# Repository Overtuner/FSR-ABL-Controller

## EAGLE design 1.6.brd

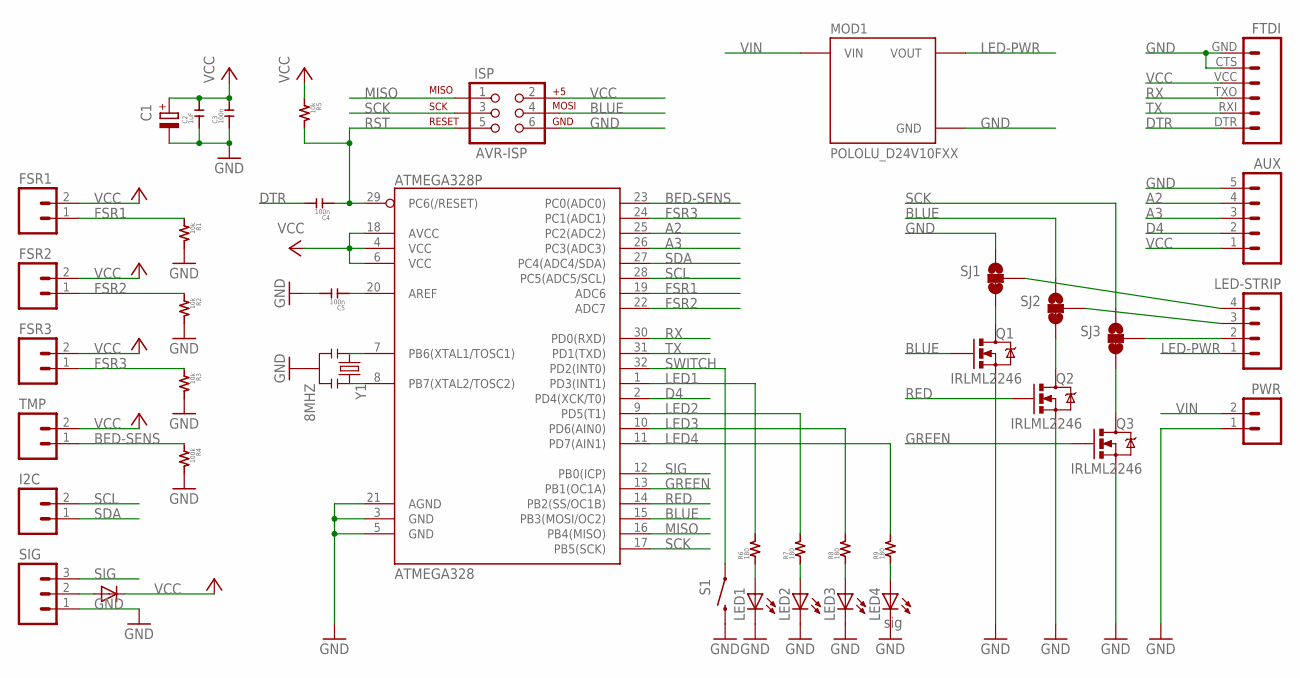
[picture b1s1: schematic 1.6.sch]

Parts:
ATMEGA328: ATMEGA328P; TQFP32-08
AUX: M05PTH; 1X05
C1: CPOL-EUSMCB; SMC_B
C2: 1uF; 0603
C3, C4, C5: 100n; 0603
D1: MBR0520LT; SOD123
FSR1, FSR2, FSR3: M02PTH; 1X02
FTDI: FTDI_BASICPTH; FTDI_BASIC
I2C: M02PTH; 1X02
ISP: AVR-ISP; 2X3_LOCK
LED1, LED2, LED3: LED3MM
LED4: sig; LED3MM
LED-STRIP: M04PTH; 1X04
MOD1: POLOLU_D24V10FXX; POLOLU_D24V10FXX_3PIN
PWR: M02PTH; 1X02
Q1, Q2, Q3: IRLML2246; SOT23
R1, R2, R3, R5: 10k; 0603
R4: 100k; 0603
R6, R7, R8, R9: 180; 0603
S1: SWITCH-MOMENTARY-2SMD; TACTILE_SWITCH_SMD
SIG: M03PTH; 1X03
SJ1, SJ2, SJ3: JUMPER-PAD-3-2OF3_NC_BY_TRACE; PAD-JUMPER-3-2OF3_NC_BY_TRACE_YES_SILK_FULL_BOX
TMP: M02PTH; 1X02
Y1: 8MHZ; RESONATOR-SMD

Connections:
A2: ATMEGA328.25 (PC2(ADC2)), AUX.4
A3: ATMEGA328.26 (PC3(ADC3)), AUX.3
AREF: ATMEGA328.20 (AREF), C5.1
BED-SENS: ATMEGA328.23 (PC0(ADC0)), R4.1, TMP.1
BLUE: ATMEGA328.15 (PB3(MOSI/OC2)), ISP.4, Q1.1 (G), SJ2.1
D4: ATMEGA328.2 (PD4(XCK/T0)), AUX.2
DTR: C4.2, FTDI.DTR (1)
FSR1: ATMEGA328.19 (ADC6), FSR1.1, R1.1
FSR2: ATMEGA328.22 (ADC7), FSR2.1, R2.1
FSR3: ATMEGA328.24 (PC1(ADC1)), FSR3.1, R3.1
GND: ATMEGA328.3 (GND), ATMEGA328.5 (GND), ATMEGA328.21 (AGND), AUX.5, C1.-, C2.1, C3.1, C5.2, FTDI.CTS (5), FTDI.GND (6), ISP.6, LED1.K (C), LED2.K (C), LED3.K (C), LED4.K (C), MOD1.GND, PWR.1, Q1.2 (S), Q2.2 (S), Q3.2 (S), R1.2, R2.2, R3.2, R4.2, S1.3 (2), S1.4 (2), SIG.1, SJ1.1, Y1.2
GREEN: ATMEGA328.13 (PB1(OC1A)), Q3.1 (G)
LED1: ATMEGA328.1 (PD3(INT1)), R6.2
LED2: ATMEGA328.9 (PD5(T1)), R7.2
LED3: ATMEGA328.10 (PD6(AIN0)), R8.2
LED4: ATMEGA328.11 (PD7(AIN1)), R9.2
LED-PWR: LED-STRIP.1, MOD1.VOUT
MISO: ATMEGA328.16 (PB4(MISO)), ISP.1
unnamed: LED1.A, R6.1
unnamed: LED2.A, R7.1
unnamed: LED3.A, R8.1
unnamed: LED4.A, R9.1
unnamed: Q1.3 (D), SJ1.3
unnamed: Q2.3 (D), SJ2.3
unnamed: D1.A, SIG.2
unnamed: Q3.3 (D), SJ3.3
unnamed: ATMEGA328.8 (PB7(XTAL2/TOSC2)), Y1.3
unnamed: ATMEGA328.7 (PB6(XTAL1/TOSC1)), Y1.1
unnamed: LED-STRIP.3, SJ2.2
unnamed: LED-STRIP.4, SJ1.2
unnamed: LED-STRIP.2, SJ3.2
RED: ATMEGA328.14 (PB2(SS/OC1B)), Q2.1 (G)
RST: ATMEGA328.29 (PC6(/RESET)), C4.1, ISP.5, R5.2
RX: ATMEGA328.30 (PD0(RXD)), FTDI.TXO (3)
SCK: ATMEGA328.17 (PB5(SCK)), ISP.3, SJ3.1
SCL: ATMEGA328.28 (PC5(ADC5/SCL)), I2C.2
SDA: ATMEGA328.27 (PC4(ADC4/SDA)), I2C.1
SIG: ATMEGA328.12 (PB0(ICP)), SIG.3
SWITCH: ATMEGA328.32 (PD2(INT0)), S1.1, S1.2 (1)
TX: ATMEGA328.31 (PD1(TXD)), FTDI.RXI (2)
VCC: ATMEGA328.4 (VCC), ATMEGA328.6 (VCC), ATMEGA328.18 (AVCC), AUX.1, C1.+, C2.2, C3.2, D1.C, FSR1.2, FSR2.2, FSR3.2, FTDI.VCC (4), ISP.2, R5.1, TMP.2
VIN: MOD1.VIN, PWR.2

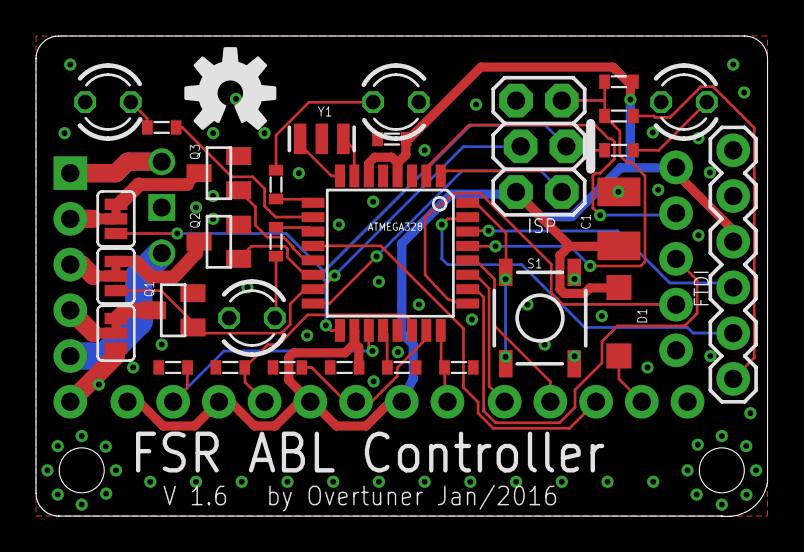
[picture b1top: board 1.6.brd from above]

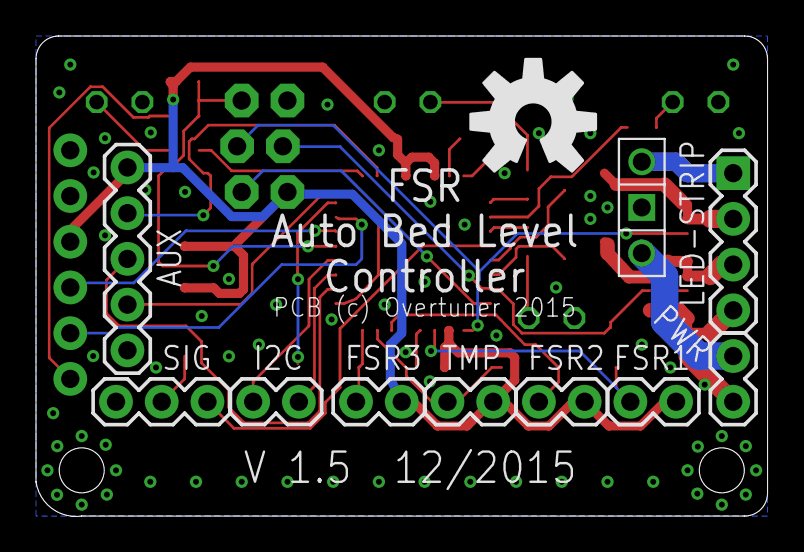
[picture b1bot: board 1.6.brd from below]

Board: 2 copper layers, 40.6 x 26.7 mm, 42 parts (11 on the bottom side), 42 nets.

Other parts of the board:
U$1: OSHW-LOGO-M
U$2: OSHW-LOGO-L

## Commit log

2016-01-30 pcb 1.5
    with fixed bug rx-tx to ftdi
2016-01-30 pcb bottom
    with and w/o buck converter for LED
2016-01-30 eagle

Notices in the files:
parts and their libraries:
SparkFun-FreqCtrl: Licensing: CC v3.0 Share-Alike You are welcome to use this library for commercial purposes.
SparkFun-Passives: Licensing: Creative Commons ShareAlike 4.0 International - https://creativecommons.org/licenses/by-sa/4.0
